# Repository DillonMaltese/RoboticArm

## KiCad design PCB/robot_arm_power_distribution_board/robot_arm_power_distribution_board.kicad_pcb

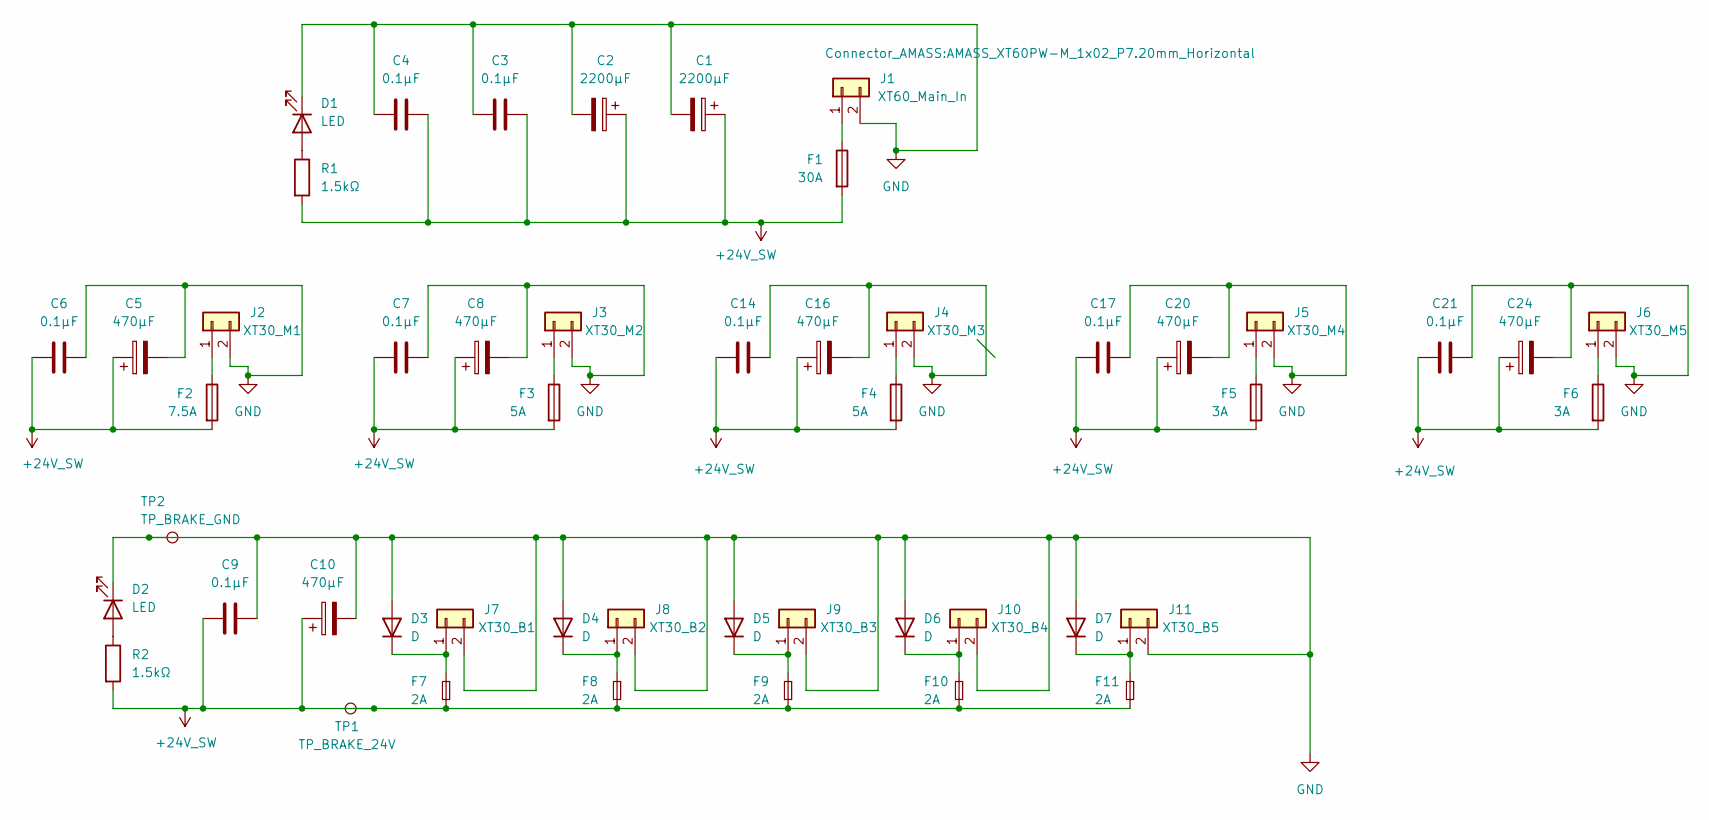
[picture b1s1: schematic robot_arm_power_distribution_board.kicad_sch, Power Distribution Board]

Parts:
C1, C2: 2200µF; CP_Radial_D18.0mm_P7.50mm
C3, C4, C6, C7, C9, C14, C17, C21: 0.1µF; C_Disc_D4.7mm_W2.5mm_P5.00mm
C5, C8, C10, C16, C20, C24: 470µF; CP_Radial_D10.0mm_P5.00mm
D1, D2: LED; LED_D5.0mm
D3, D4, D5, D6, D7: D; DO-201AD_VIS
F1: 30A; CONN_3557-2_KEY
F2: 7.5A; CONN_3557-2_KEY
F3, F4: 5A; CONN_3557-2_KEY
F5, F6: 3A; CONN_3557-2_KEY
F7, F8, F9, F10, F11: 2A; FUSE_05200101Z_LTF
J1: XT60_Main_In; AMASS_XT60PW-M_1x02_P7.20mm_Horizontal
J2: XT30_M1; AMASS_XT30UPB-M
J3: XT30_M2; AMASS_XT30UPB-M
J4: XT30_M3; AMASS_XT30UPB-M
J5: XT30_M4; AMASS_XT30UPB-M
J6: XT30_M5; AMASS_XT30UPB-M
J7: XT30_B1; AMASS_XT30UPB-M
J8: XT30_B2; AMASS_XT30UPB-M
J9: XT30_B3; AMASS_XT30UPB-M
J10: XT30_B4; AMASS_XT30UPB-M
J11: XT30_B5; AMASS_XT30UPB-M
R1, R2: 1.5kΩ; R_Axial_DIN0207_L6.3mm_D2.5mm_P10.16mm_Horizontal
TP1: TP_BRAKE_24V; TestPoint_THTPad_1.5x1.5mm_Drill0.7mm
TP2: TP_BRAKE_GND; TestPoint_THTPad_1.5x1.5mm_Drill0.7mm

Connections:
+24V_SW: C1.1, C2.1, C3.2, C4.2, C5.1, C6.1, C7.1, C8.1, C9.1, C10.1, C14.1, C16.1, C17.1, C20.1, C21.1, C24.1, F1.2, F2.2, F3.2, F4.2, F5.2, F6.2, F7.2, F8.2, F9.2, F10.2, F11.2, R1.2, R2.2, TP1.1 (1_1)
GND: C1.2, C2.2, C3.1, C4.1, C5.2, C6.2, C7.2, C8.2, C9.2, C10.2, C14.2, C16.2, C17.2, C20.2, C21.2, C24.2, D1.1 (K), D2.1 (K), D3.2 (A), D4.2 (A), D5.2 (A), D6.2 (A), D7.2 (A), J1.2, J2.2, J3.2, J4.2, J5.2, J6.2, J7.2, J8.2, J9.2, J10.2, J11.2, TP2.1 (1_1)
unnamed: D1.2 (A), R1.1
unnamed: D2.2 (A), R2.1
unnamed: D3.1 (K), F7.1, J7.1
unnamed: D4.1 (K), F8.1, J8.1
unnamed: D5.1 (K), F9.1, J9.1
unnamed: D6.1 (K), F10.1, J10.1
unnamed: D7.1 (K), F11.1, J11.1
unnamed: F1.1, J1.1
unnamed: F2.1, J2.1
unnamed: F3.1, J3.1
unnamed: F4.1, J4.1
unnamed: F5.1, J5.1
unnamed: F6.1, J6.1

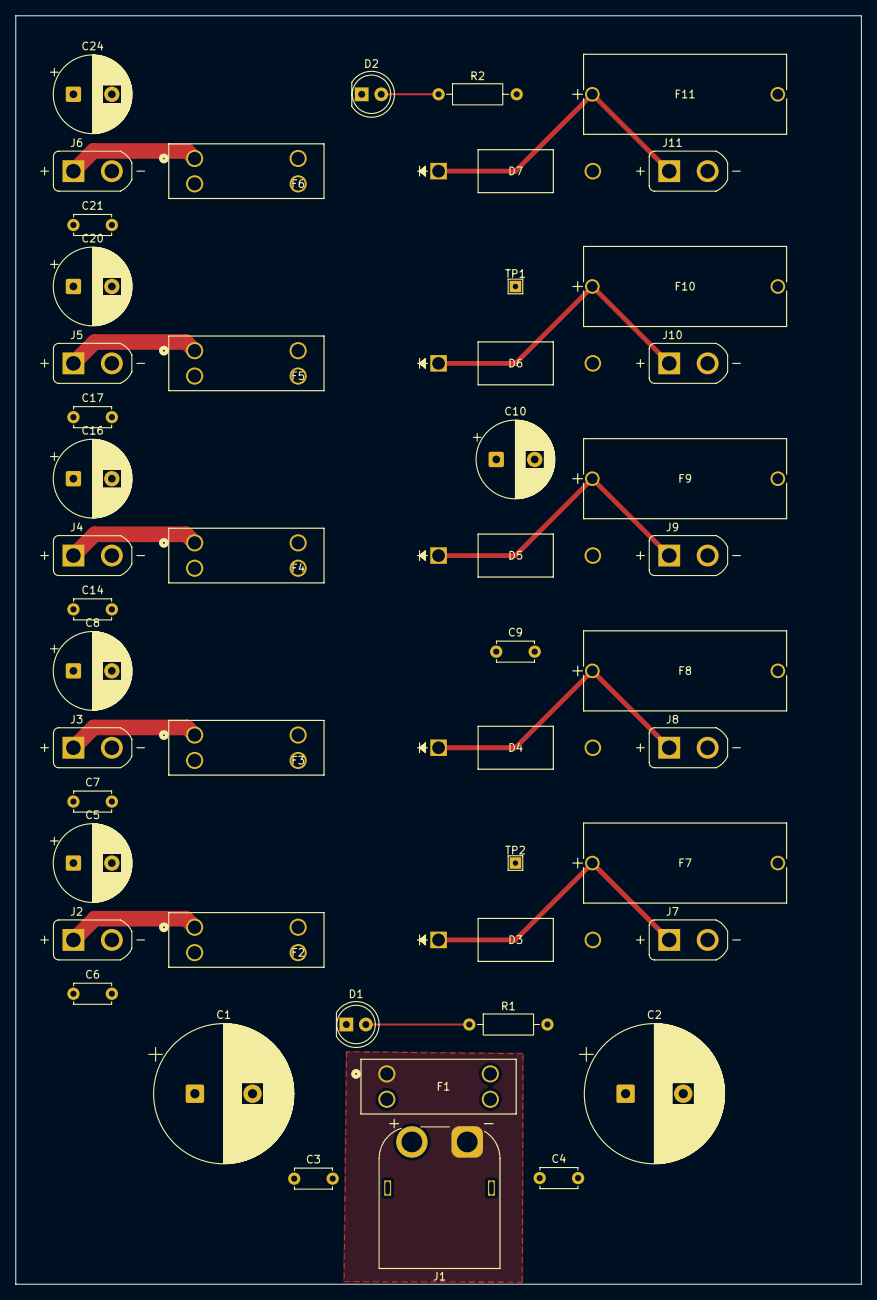
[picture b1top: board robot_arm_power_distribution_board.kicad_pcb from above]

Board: 4 copper layers, 110.0 x 165.0 mm, 49 parts (0 on the bottom side), 15 nets.

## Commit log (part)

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2025-06-25 Switching to Pop OS
2025-07-09 Starting some recognition stuff
2025-10-18 Started working with final arm
2025-11-13 Starting inverse kinematics
2025-12-25 Inverse kinematics work
2026-01-08 Learning Inverse Kinematics
2026-01-08 Almost done with IK lesson
2026-01-10 Still working
2026-01-11 Think I finish just need to test
2026-01-18 Hopefully finished just need to add comments and test it
2026-02-27 Just some cleanup
2026-03-10 Finished all inverse kinematics now on to main Arduino code
2026-03-10 Finished with code before CSEF
